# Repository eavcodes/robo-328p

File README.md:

# robo 328P
Projeto de placa com atmega 328P para estudo de sensores e robótica - Feito com KiCAD

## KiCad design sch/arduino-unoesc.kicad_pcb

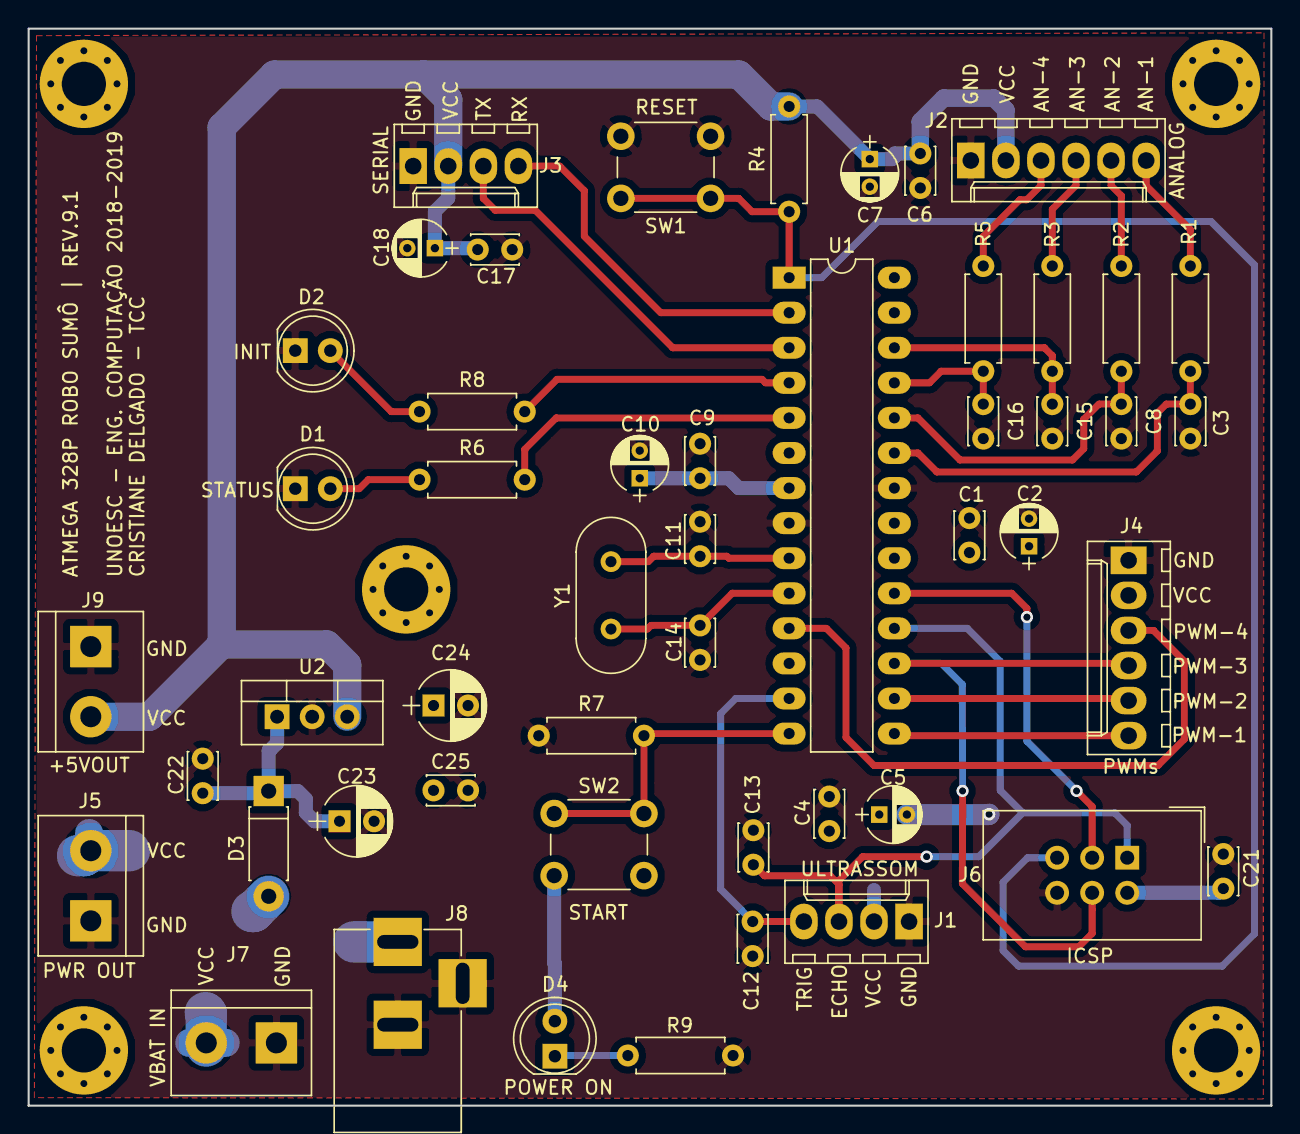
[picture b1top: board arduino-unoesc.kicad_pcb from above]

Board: 2 copper layers, 90.0 x 78.0 mm, 50 parts (0 on the bottom side), 30 nets.

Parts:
C1, C4, C6, C9, C17, C21, C22, C25: 0.1uF; C_Disc_D3.4mm_W2.1mm_P2.50mm
C2, C5, C7, C10, C18: 10uF; CP_Radial_D4.0mm_P2.00mm
C3, C8, C15, C16: 0.22u; C_Disc_D3.4mm_W2.1mm_P2.50mm
C11, C14: 22pF; C_Disc_D3.4mm_W2.1mm_P2.50mm
C12, C13: 100pF; C_Disc_D3.4mm_W2.1mm_P2.50mm
C23: 100uF; CP_Radial_D5.0mm_P2.50mm
C24: 47uF; CP_Radial_D5.0mm_P2.50mm
D1: STATUS; LED_D5.0mm
D2: INIT; LED_D5.0mm
D3: 1N4007; D_DO-41_SOD81_P7.62mm_Horizontal
D4: PWR; LED_D5.0mm
J1: ultrassom; Molex_KK-6410-04_04x2.54mm_Straight
J2: reflectancia-entrada; Molex_KK-6410-06_06x2.54mm_Straight
J3: SERIAL UART; Molex_KK-6410-04_04x2.54mm_Straight
J4: ponte H PWM; Molex_KK-6410-06_06x2.54mm_Straight
J5: PWR OUT; TerminalBlock_bornier-2_P5.08mm
J6: ICSP2; IDC-Header_2x03_Pitch2.54mm_Straight
J7: PWR IN; TerminalBlock_bornier-2_P5.08mm
J8: PWR JACK; BARREL_JACK
J9: 5VOUT; TerminalBlock_bornier-2_P5.08mm
R1, R2, R3, R5: 1k; R_Axial_DIN0207_L6.3mm_D2.5mm_P7.62mm_Horizontal
R4, R7: 10k; R_Axial_DIN0207_L6.3mm_D2.5mm_P7.62mm_Horizontal
R6, R8, R9: 470R; R_Axial_DIN0207_L6.3mm_D2.5mm_P7.62mm_Horizontal
SW1: RESET; SW_PUSH_6mm_h4.3mm
SW2: START; SW_PUSH_6mm_h4.3mm
U1: ATmega328P-PU; DIP-28_W7.62mm_LongPads
U2: LM7805_TO220; TO-220-3_Vertical
Y1: 16Mhz; Crystal_HC49-U_Vertical

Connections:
+5V: C1.1, C2.1, C4.1, C5.1, C6.1, C7.1, C9.1, C10.1, C17.1, C18.1, C21.1, C24.1, C25.1, D4.2, J1.2, J2.2, J3.2, J4.2, J6.2, J9.2, R4.2, SW2.2, U1.7, U1.20, U1.21, U2.3
/328P_ICSP_MIS0: C13.1, J1.3, J6.1, U1.18
/328P_ICSP_MOSI: J4.4, J6.4, U1.17
/328P_ICSP_RESET: J6.5, R4.1, SW1.1, U1.1
/328P_ICSP_SCK: J6.3, U1.19
/INIT: R8.2, U1.4
/PWM-1: J4.6, U1.15
/PWM-2: J4.5, U1.16
/PWM-4: J4.3, U1.11
/REFLECT-1: C3.1, R1.2, U1.23
/REFLECT-1IN: J2.6, R1.1
/REFLECT-2: C8.1, R2.2, U1.24
/REFLECT-2IN: J2.5, R2.1
/REFLECT-3: C15.1, R3.2, U1.26
/REFLECT-3IN: J2.4, R3.1
/REFLECT-4: C16.1, R5.2, U1.25
/REFLECT-4IN: J2.3, R5.1
/START: R7.2, SW2.1, U1.14
/UART_RX: J3.4, U1.2
/UART_TX: J3.3, U1.3
/ULTRASONIC-TRIGGER: C12.1, J1.4, U1.13
GND: C1.2, C2.2, C3.2, C4.2, C5.2, C6.2, C7.2, C8.2, C9.2, C10.2, C11.1, C12.2, C13.2, C14.1, C15.2, C16.2, C17.2, C18.2, C21.2, C22.2, C23.2, C24.2, C25.2, D1.1, D2.1, J1.1, J2.1, J3.1, J4.1, J5.1, J6.6, J7.1, J8.2, J8.3, J9.1, R7.1, R9.1, SW1.2, U1.8, U1.22, U2.2
unnamed: C11.2, U1.9, Y1.2
unnamed: C14.2, U1.10, Y1.1
unnamed: C22.1, C23.1, D3.1, U2.1
unnamed: D1.2, R6.1
unnamed: D2.2, R8.1
unnamed: D3.2, J5.2, J7.2, J8.1
unnamed: D4.1, R9.2
unnamed: R6.2, U1.5

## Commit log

2019-06-03 Set theme jekyll-theme-slate
2019-06-03 revisao 9.1
    Versao publicada pela estudante Cristiane Delgado da Unoesc como parte do circuito elaborado durante o trabalho de conclusão de curso em eng. de computação.
